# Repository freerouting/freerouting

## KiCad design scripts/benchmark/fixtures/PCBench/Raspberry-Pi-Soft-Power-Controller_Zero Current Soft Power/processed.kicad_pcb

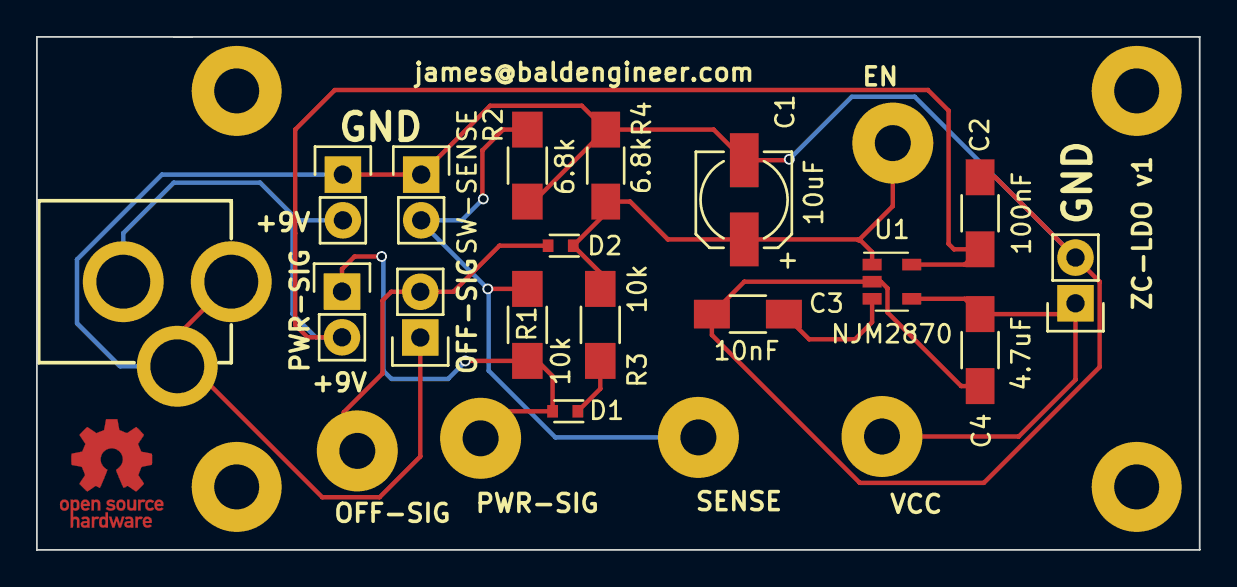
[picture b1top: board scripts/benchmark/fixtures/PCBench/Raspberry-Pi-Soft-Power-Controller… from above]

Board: 2 copper layers, 64.6 x 28.5 mm, 22 parts (0 on the bottom side), 9 nets.

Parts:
C1: 10uF; c_elec_5x5.3
C2: 100nF; C_1206_HandSoldering
C3: 10nF; C_1206_HandSoldering
C4: 4.7uF; C_1206_HandSoldering
D1, D2: 1SS389; SOD-523
J1: PWR-SIG; Pin_Header_Straight_1x02
J2: SW-SENSE; Pin_Header_Straight_1x02
J3: 9V-IN; Pin_Header_Straight_1x02
J4: SENSE; SolderWirePad_single_2mmDrill
J5: OFF-SIG; Pin_Header_Straight_1x02
J6: TEST_1P; SolderWirePad_single_2mmDrill
J7: OFF-SIG; SolderWirePad_single_2mmDrill
J8: EN; SolderWirePad_single_2mmDrill
J9: VCC; SolderWirePad_single_2mmDrill
J10: AVR-VCC; Pin_Header_Straight_1x02
J11: 9V-BJ; POWER_JACK_PTH
R1, R3: 10k; R_1206_HandSoldering
R2: 6.8k; R_1206_HandSoldering
R4: 6.8k; C_1206_HandSoldering
U1: NJM2870; SOT-23-5

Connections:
+9V: C2.1, J1.2, J3.2, J11.1, U1.5
/LC-VCC: C4.1, J9.1, J10.1, U1.4
/OFF-SIG: D2.2, J5.2, J7.1
/PWR-SIG: D1.2, J1.1, J6.1, R1.2
/SW-SENSE: J2.2, J4.1, R1.1, R2.2
GND: C1.2, C2.2, C3.2, C4.2, J2.1, J3.1, J5.1, J10.2, J11.2, J11.3, R2.1, R4.1, U1.2
unnamed: C1.1, D2.1, J8.1, R3.1, R4.2, U1.1
unnamed: C3.1, U1.3
unnamed: D1.1, R3.2

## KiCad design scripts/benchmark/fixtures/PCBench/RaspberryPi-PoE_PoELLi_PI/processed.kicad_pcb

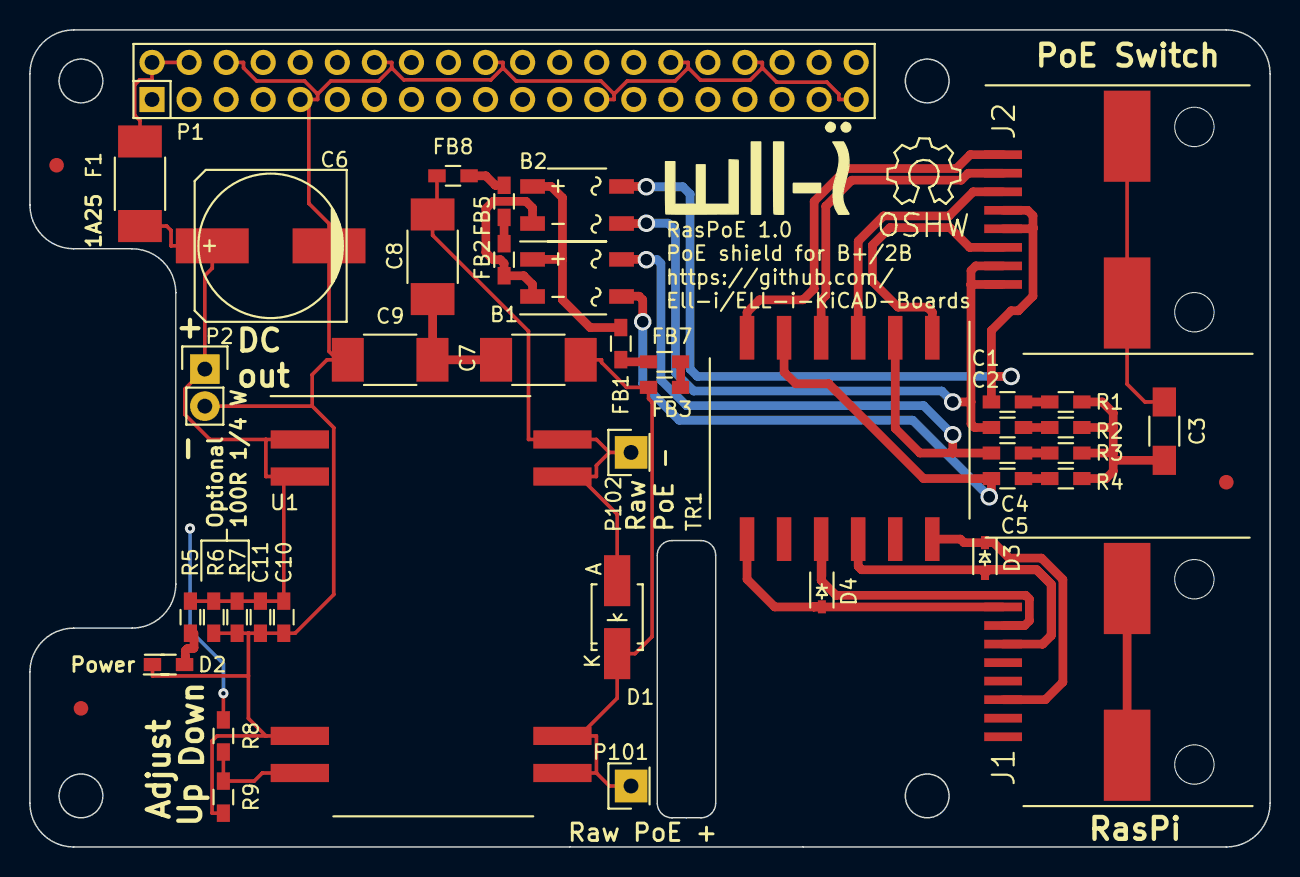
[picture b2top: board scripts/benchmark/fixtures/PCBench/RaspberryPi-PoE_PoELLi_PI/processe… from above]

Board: 2 copper layers, 85.0 x 56.0 mm, 46 parts (0 on the bottom side), 32 nets.

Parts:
B1, B2: MB110S; TO-269AA
C1, C2, C4, C5: 10n 100V; R_0603_HandSoldering
C3: 1n 2kV; C_1206_HandSoldering
C6: 470u; c_elec_10x10
C7, C8, C9: 4n7 2kV; C_1812_HandSoldering
C10: 10n; R_0603_HandSoldering
C11: 10u; R_0603_HandSoldering
D1: SMA58; Diode-SMA_Handsoldering
D2: LED; R_0603_HandSoldering
D3, D4: TVS; SOD-323
F1: FUSE; C_1812_HandSoldering
FB1, FB2, FB3, FB5, FB7, FB8: FILTER; R_0603_HandSoldering
FID1, FID2, FID3: 1, 2 mm; Fiducial_2mm_dia
J1: RJSSE-5080; RJSSE-5380
J2: RJSSE-5380
LOGO101: OPEN_HARDWARE_1; Symbol_OSHW-Logo_SilkScreen
LOGO102: ELL-i; ELL-i_large
P1: CONN_02X20; Pin_Header_Straight_2x20
P2: CONN_01X02; Pin_Header_Straight_1x02
P101, P102: CONN_01X01; Pin_Header_Straight_1x01
R1, R2, R3, R4: 75R; R_0603_HandSoldering
R5: 180R; R_0603_HandSoldering
R6, R7: 100R 250 mW; R_0603_HandSoldering
R8, R9: R; R_0603_HandSoldering
TR1: 749012011; WE_749012011
U1: AG9800

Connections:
+5V: F1.2, P1.2, P1.4
/ADJ: R8.2, R9.1, U1.4
/AG_IN_+: C7.1, D1.2, FB7.2, P101.1, U1.5, U1.6
/AG_IN_-: C8.1, D1.1, FB8.2, P102.1, U1.7, U1.8
/AG_OUT_+: C6.1, C10.1, C11.1, F1.1, P2.1, R5.1, R6.1, R7.1, U1.1, U1.2
/POE_A+: B1.2, C5.1, TR1.5
/POE_A-: B1.4, C4.1, TR1.2
/POE_B+: B2.2, C2.1, J2.7, J2.8
/POE_B-: B2.4, C1.1, J2.4, J2.5
/RD+: D3.2, J1.3, TR1.10
/RD-: D3.1, J1.6, TR1.12
/RX+: J2.3, TR1.3
/RX-: J2.6, TR1.1
/TD+: D4.2, J1.1, TR1.7
/TD-: D4.1, J1.2, TR1.9
/TX+: J2.1, TR1.6
/TX-: J2.2, TR1.4
/VIN: B1.3, B2.3, FB1.1
GND: C6.2, C9.1, C10.2, C11.2, D2.2, P1.6, P1.9, P1.14, P1.20, P1.25, P1.30, P1.34, P1.39, P2.2, R6.2, R7.2, R9.2, U1.3
GNDA: C3.2, J2.9
GNDD: B1.1, B2.1, FB2.1
unnamed: C1.2, R1.1
unnamed: C2.2, R2.1
unnamed: C3.1, R1.2, R2.2, R3.2, R4.2
unnamed: C4.2, R3.1
unnamed: C5.2, R4.1
unnamed: C7.2, C8.2, C9.2
unnamed: D2.1, R5.2
unnamed: FB1.2, FB3.1
unnamed: FB2.2, FB5.1
unnamed: FB3.2, FB7.1
unnamed: FB5.2, FB8.1

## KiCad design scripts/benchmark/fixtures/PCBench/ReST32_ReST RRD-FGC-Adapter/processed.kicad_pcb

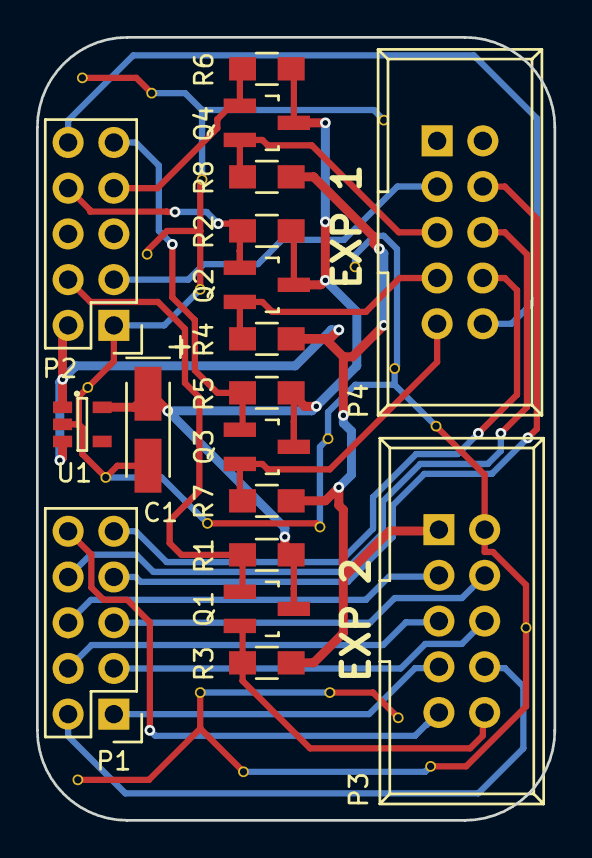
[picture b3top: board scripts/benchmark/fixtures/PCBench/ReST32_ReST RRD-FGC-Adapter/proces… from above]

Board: 2 copper layers, 28.8 x 43.5 mm, 18 parts (0 on the bottom side), 23 nets.

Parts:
C1: 2.2uF; TantalC_SizeA_EIA-3216_HandSoldering
P1, P2: CONN_02X05; Pin_Header_Straight_2x05
P3, P4: CONN_02X05; IDC_Header_Straight_10pins
Q1, Q2, Q3, Q4: BSS138; SOT-23_Handsoldering
R1, R2, R3, R4, R5, R6, R7, R8: 10K; R_0805_HandSoldering
U1: MIC5205; SOT-23-5

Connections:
+3V3: C1.1, Q1.3, Q2.3, Q3.3, Q4.3, R1.1, R2.1, R5.1, R6.1, U1.5
+5V: P2.2, P3.1, R3.1, R4.1, R7.1, R8.1, U1.1, U1.3
/BEEP: P3.10, Q1.2, R3.2
/CS: P4.7, Q2.2, R4.2
/DISPLAY_CD: P1.2, P3.8
/DISPLAY_CS: P1.1, P3.7
/DISPLAY_D0: P1.4, P3.5
/DISPLAY_D1: P1.3, P3.6
/DISPLAY_D2: P1.6, P3.3
/DISPLAY_D3: P1.5, P3.4
/DISPLAY_D4: P1.8, P4.6
/DISPLAY_D5: P1.7, P4.4
/DISPLAY_D6: P1.10, P3.9
/DISPLAY_D7: P1.9, P4.8
/DISPLAY_RD: P2.3, P4.3
/DISPLAY_WR: P2.4, Q1.1, R1.2
/MISO: P2.10, P4.10
/MOSI: P4.5, Q4.2, R8.2
/SCK: P4.9, Q3.2, R7.2
/SPI_CS1: P2.8, Q2.1, R2.2
/SPI_MOSI: P2.7, Q4.1, R6.2
/SPI_SCK: P2.9, Q3.1, R5.2
GND: C1.2, P2.1, P3.2, U1.2
